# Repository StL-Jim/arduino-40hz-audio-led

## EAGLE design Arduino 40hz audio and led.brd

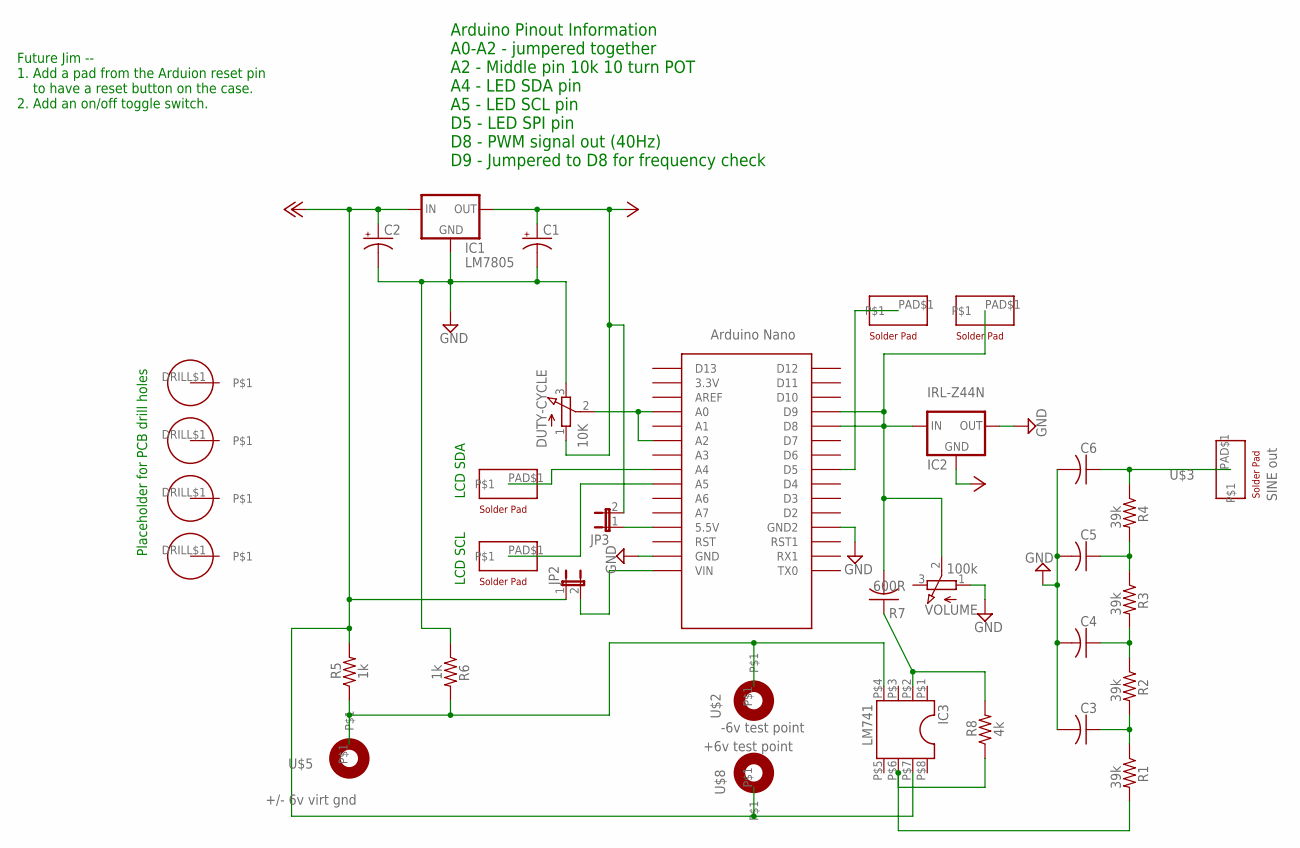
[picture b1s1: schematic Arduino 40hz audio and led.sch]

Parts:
C1: 10uF; CPOL-RADIAL-1000UF-25V
C2: 100uF; CPOL-RADIAL-1000UF-25V
C3, C4, C5, C6: 100nF; C050-025X075
DUTY-CYCLE: 10K; POTENTIOMETER-THRUHOLE
IC1: LM7805; 78XXL
IC2: IRL-Z44N; 78XXL
IC3: LM741; DIL08-THRUHOLE
JP2, JP3: JUMPER-JP1ETHRUHOLE; JP1-THRUHOLE
P+1: +12VTHRUHOLE; POWER-IN-PAD-THRUHOLE
P+2: +5VTHRUHOLE; POWER-IN-PAD-THRUHOLE
P+3: +6VTHRUHOLE; POWER-IN-PAD-THRUHOLE
R1, R2, R3, R4: 39k; AXIAL-0.4
R5, R6: 1k; AXIAL-0.4
R7: 600R; C050-025X075
R8: 4k; AXIAL-0.4
U$1: ARDUINO-NANOTHRUHOLE; ARDUINO-NANO-THRUHOLE
U$2: -6v test point; PROBE_POINT_1-THRUHOLE
U$3: SINE out; PAD-RECTANGLE-175MIL-THRUHOLE
U$4: SCL; PAD-RECTANGLE-175MIL-THRUHOLE
U$5: +/- 6v virt gnd; PROBE_POINT_1-THRUHOLE
U$6, U$9, U$14: PAD-1PIN-RECTANGLE175; PAD-RECTANGLE-175MIL-THRUHOLE
U$8: +6v test point; PROBE_POINT_1-THRUHOLE
U$10, U$11, U$12, U$13: DRILL-HOLE-4MMTHRUHOLE; DRILL-HOLE-4MM-THRUHOLE
VOLUME: 100k; POTENTIOMETER-THRUHOLE

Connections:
+5V: C1.1 (+), DUTY-CYCLE.1 (A), IC1.OUT, IC2.GND, JP3.2, P+2.VCC, P+3.VCC
+12V: C2.1 (+), IC1.IN, IC3.P$7 (7), JP2.1, P+1.VCC, R5.P$2 (2), U$8.P$1
GND: C1.2 (-), C2.2 (-), C3.2, C4.2, C5.2, C6.2, DUTY-CYCLE.3 (E), IC1.GND, IC2.OUT, R6.P$1 (1), U$1.GND, U$1.GND1 (GND2), VOLUME.1 (A)
unnamed: DUTY-CYCLE.2 (S), U$1.A0, U$1.A2
unnamed: IC2.IN, R7.2, U$1.D8, U$1.D9, U$14.PAD$1, VOLUME.2 (S)
unnamed: C3.1, R1.P$1 (1), R2.P$2 (2)
unnamed: C4.1, R2.P$1 (1), R3.P$2 (2)
unnamed: C5.1, R3.P$1 (1), R4.P$2 (2)
unnamed: C6.1, R4.P$1 (1), U$3.PAD$1
unnamed: JP2.2, U$1.RAW (VIN)
unnamed: JP3.1, U$1.5V (5.5V)
unnamed: IC3.P$2 (2), R7.1, R8.P$2 (2)
unnamed: U$1.D5, U$9.PAD$1
unnamed: IC3.P$4 (4), R5.P$1 (1), R6.P$2 (2), U$2.P$1, U$5.P$1
unnamed: IC3.P$6 (6), R1.P$2 (2), R8.P$1 (1)
unnamed: U$1.A4, U$4.PAD$1
unnamed: U$1.A5, U$6.PAD$1

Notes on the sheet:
Arduino Pinout Information A0-A2 - jumpered together A2 - Middle pin 10k 10 turn POT A4 - LED SDA pin A5 - LED SCL pin D5 - LED SPI pin D8 - PWM signal out (40Hz) D9 - Jumpered to D8 for frequency check
Placeholder for PCB drill holes
LCD SDA
LCD SCL
Future Jim -- 1. Add a pad from the Arduion reset pin to have a reset button on the case. 2. Add an on/off toggle switch.

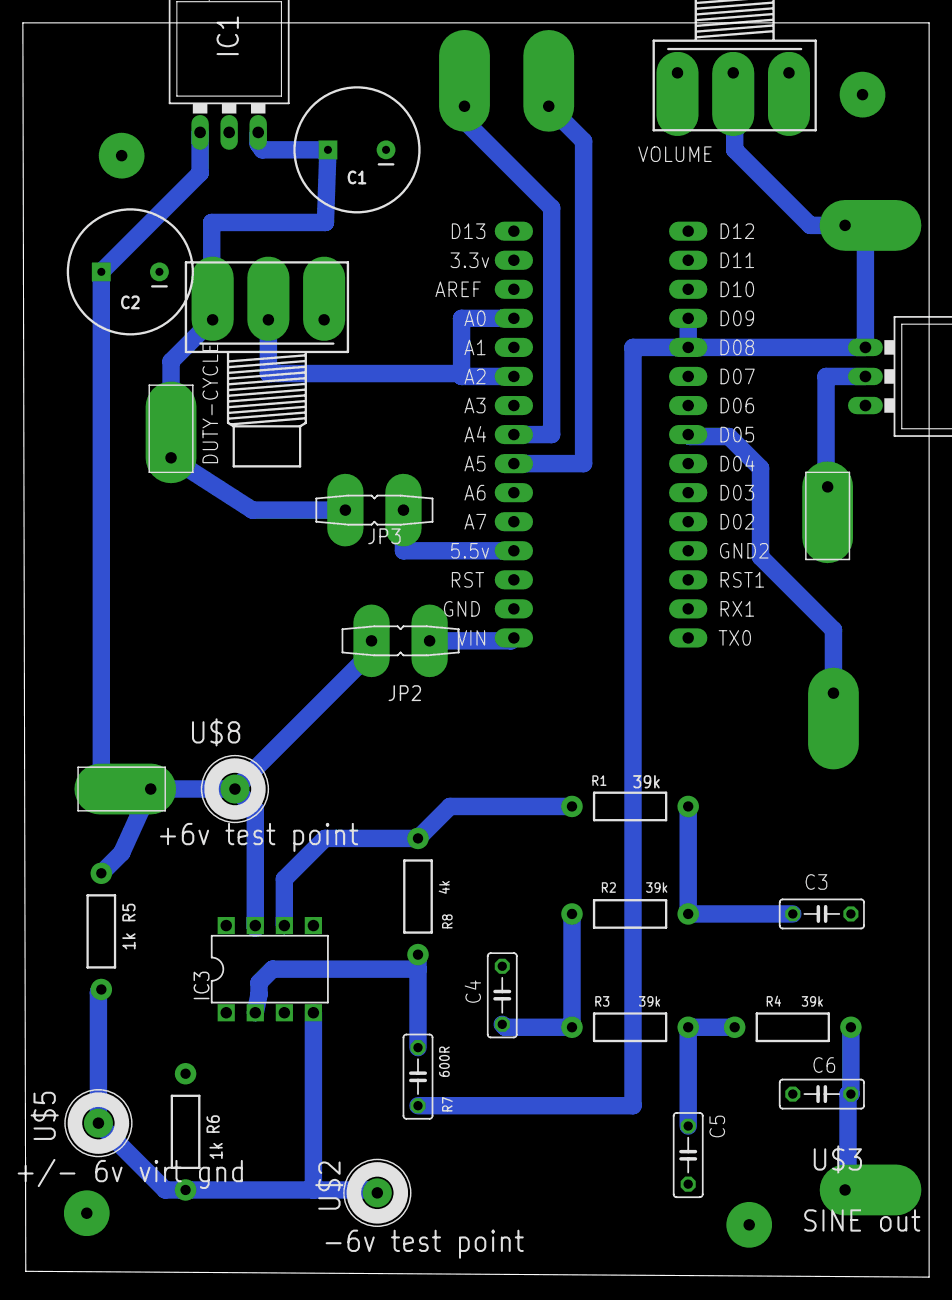
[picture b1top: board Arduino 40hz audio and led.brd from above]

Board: 2 copper layers, 79.2 x 109.7 mm, 37 parts (0 on the bottom side), 17 nets.

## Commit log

2019-05-26 Initial commit of a basic schematic
    Initial commit of a basic schematic
2019-05-26 Initial schmatic and layout of board
    Initial schmatic and layout of board
    Still need to move some things around, add a couple of pads and change
    some pad sizes.
2019-05-26 Updated schematic and board
    Updated schematic and board. Made the board more compact.
    Still need to fix a few issues with the board
2019-05-27 Version 1 is done.. w00t
    Version 1 is done.. w00t!!!
    Now I need to make some little fixes as I've built the first one.
2019-05-27 Tagging this v1.0.1
    Tagging this v1.0.1.
    * Fixed the +/- 6v traces and placement.
    * Changed a few pads to be larger
    * Added a pad for the LED out signal from D5
    * Removed Jumper JP1
    * Added drill holes, those this will vary until you have exact PCB board
2019-06-06 This will be the final version of design
    This will be the final version of design unless I come up with something
    more amazing. At this point I will just be making minor tweaks.
    The next phase of this effort will be to go from sine to square via a
    Schmitt trigger.
2019-07-30 Minor updates
    Minor updates, mainly to texted in the schematic.
2019-08-09 Created new branch for CNC tool path
    Created new branch for CNC tool pathing. The major changes are to trace
    width and clearances for cnc milling.
    Figers crossed!
    On branch cncToolPath
    Changes to be committed:
    modified: Arduino 40hz audio and led.b#1
2019-08-09 Not sure what changed here
    Not sure what changed here.
    That's what I get for not immediately committing changes
    On branch master
    Changes to be committed:
    modified: eagle.epf
2019-08-30 Should be final surface mount commit
    This should be the final surface mount commit before making a new
    version of the board with 'proper' through hole parts.
2019-09-15 First commit after creating thruhole branch
    This is the first commit after changing parts and the board for a
    thru-hole design.
2019-10-06 See Diff for changes
2019-10-12 First version of moving traces to the bottom.
    First version of moving traces to the bottom.
    Now to figure out how to mill this correctly, I'm guessing I need to
    mirror it when I do the tools. Anyway future Jim will judge how this
    went.
2019-10-19 Big update to this branch
    Big update to this branch. This branch I've completed the layout of the
    board for single sided copper, where the parts are on top (no copper)
    and the traces are on the bottom (copper layer).
    I've worked quite a bit at setting trace width, spacing and part
    spacing.
2019-10-19 Adding design rule chanes
    Adding design rule chanes
2019-10-19 Removed some CAM files
    Removed some CAM files that were in the wrong place, and had been
    added to revision control.

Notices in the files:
parts and their libraries:
SparkFun-PowerIC: Licensing: Creative Commons ShareAlike 4.0 International - https://creativecommons.org/licenses/by-sa/4.0
